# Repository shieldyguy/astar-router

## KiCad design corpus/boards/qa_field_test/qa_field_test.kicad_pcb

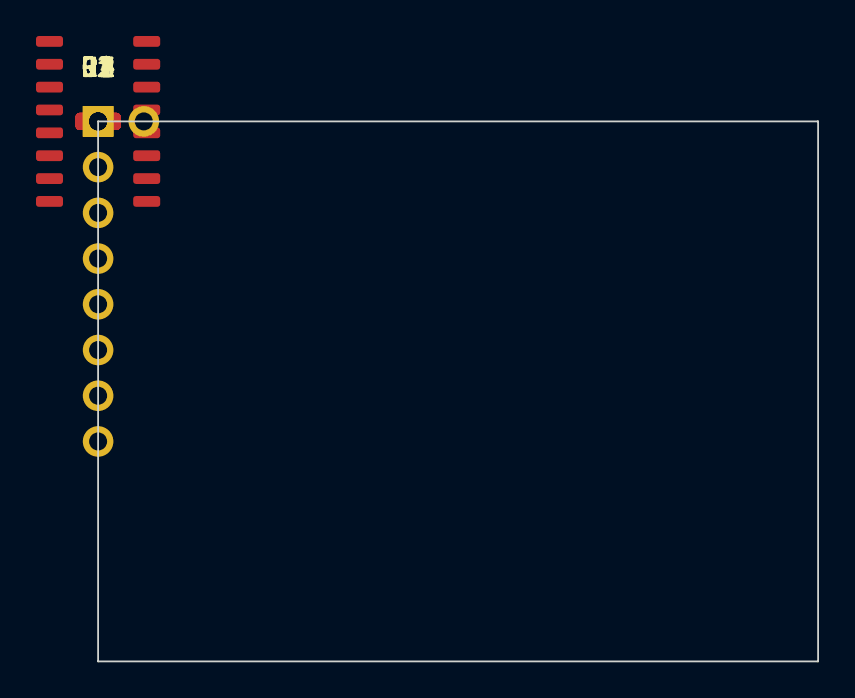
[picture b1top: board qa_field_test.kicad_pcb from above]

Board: 4 copper layers, 40.0 x 30.0 mm, 8 parts (0 on the bottom side), 14 nets, no tracks yet.

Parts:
C1: C_0603
J1: Header_1x8
J2: Header_1x2
R1, R2, R3, R4: R_0603
U1: SOIC16

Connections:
+3V3: C1.1, J2.1, U1.9, U1.15
GND: C1.2, J2.2, R1.2, R2.2, R3.2, R4.2, U1.10, U1.16
S1: J1.1, U1.1
S2: J1.2, U1.2
S3: J1.3, U1.3
S4: J1.4, U1.4
S5: J1.5, U1.5
S6: J1.6, U1.6
S7: J1.7, U1.7
S8: J1.8, U1.8
T1: R1.1, U1.14
T2: R2.1, U1.13
T3: R3.1, U1.12
T4: R4.1, U1.11

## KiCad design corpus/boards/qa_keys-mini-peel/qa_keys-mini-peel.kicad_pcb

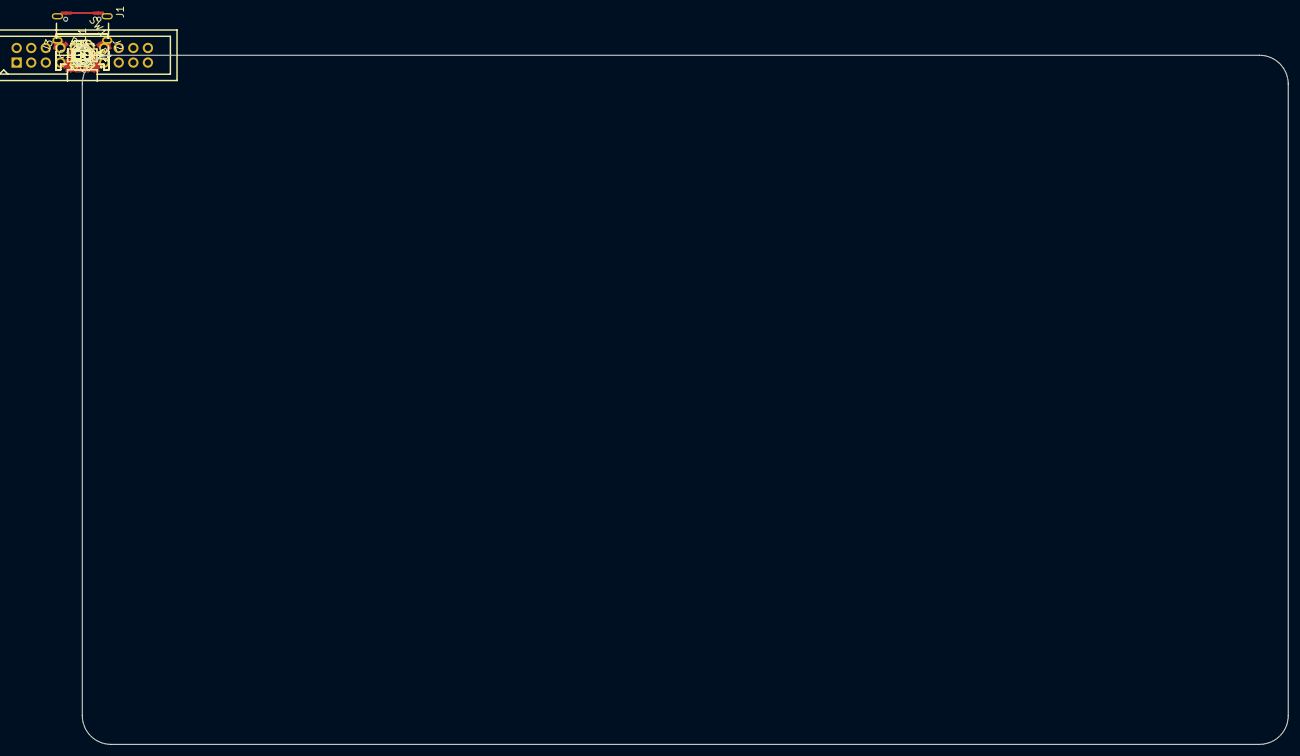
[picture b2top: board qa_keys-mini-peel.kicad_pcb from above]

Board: 4 copper layers, 210.0 x 120.0 mm, 16 parts (0 on the bottom side), 33 nets, no tracks yet.

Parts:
C1: 100nF; CC0603KRX7R9BB104
C3: 10uF; CL31B106KAHNNNE
D1, D2: B5819W SL; B5819W_SL
D3: RED; KT-0603R
J1: USB-C; TYPE-C_16PIN_2MD(073)
J2: DN; S4B-ZR-SM4A-TF(LF)(SN)
J3: UP; S4B-ZR-SM4A-TF(LF)(SN)
J4: KEY37; 2.54-2*10P
P9: P9
R1, R2: 5.1kΩ; 0603WAF5101T5E
R3: 10kΩ; 0603WAF1002T5E
R4: 1kΩ; 0603WAF1001T5E
SW1: BOOT; TS-1187A-B-A-B
U1: CH32X035G8U6

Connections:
+5V: C1.1, C3.1, D1.1, D2.1, J3.1, SW1.3, U1.2
/BR4: J4.1, U1.10
/BR5: J4.5, U1.14
/BR6: J4.9, U1.17
/BR7: J4.13, U1.20
/BR8: P9.2, U1.25
/LED: R4.1, U1.1
/MK4: J4.3, U1.12
/MK5: J4.7, U1.15
/MK6: J4.11, U1.18
/MK7: J4.15, U1.23
/MK8: P9.1, U1.28
/SCAN0: J4.2, U1.9
/SCAN1: J4.4, U1.11
/SCAN2: J4.6, U1.13
/SCAN3: J4.8, U1.6
/SCAN4: J4.10, U1.16
/SCAN5: J4.12, U1.19
/SCAN6: J4.14, U1.3
/SCAN7: J4.16, U1.24
/U1RX: J2.2, U1.22
/U1TX: J2.3, U1.21
/U2RX: J3.3, U1.8
/U2TX: J3.2, U1.7
/USB_DM: J1.A7, J1.B7, U1.26
/USB_DP: J1.A6, J1.B6, R3.1, U1.27
GND: C1.2, C3.2, D3.2, J1.13, J1.14, J1.A1B12, J1.B1A12, J2.4, J2.5, J2.6, J3.4, J3.5, J3.6, R1.2, R2.2, U1.29
unnamed: D3.1, R4.2
unnamed: J1.A5, R1.1
unnamed: J1.B5, R2.1
unnamed: R3.2, SW1.1
V5_BUOY: D2.2, J2.1
V5_USB: D1.2, J1.A4B9, J1.B4A9
